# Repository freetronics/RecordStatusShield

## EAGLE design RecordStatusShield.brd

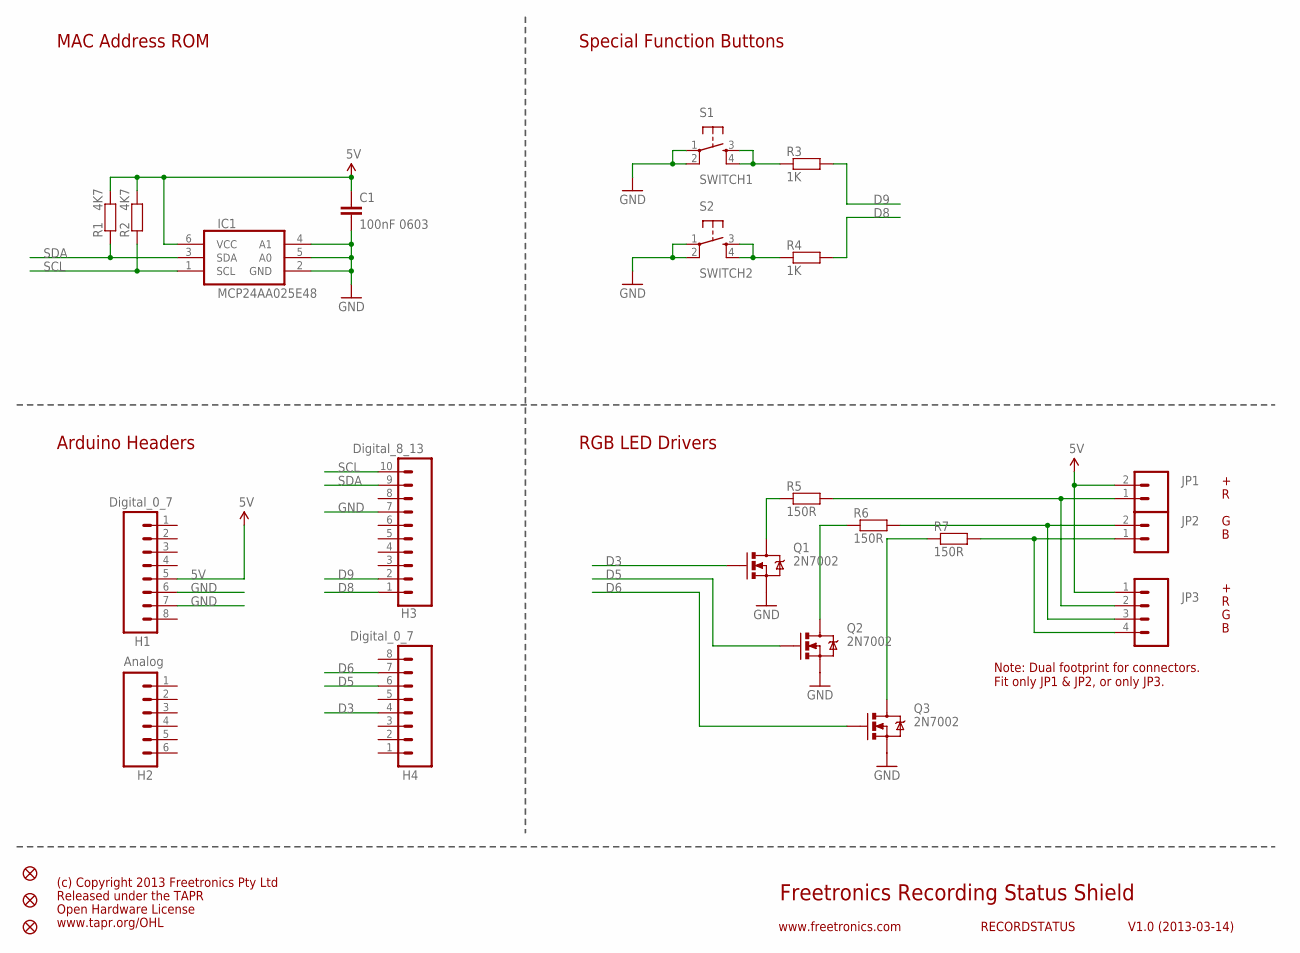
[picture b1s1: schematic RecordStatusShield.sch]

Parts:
C1: 100nF 0603; C0603
FID5, FID6, FID7: FIDUCIAL1X2.5; FIDUCIAL-1X2.5
H1, H4: Digital_0_7; 1X08
H2: Analog; 1X06
H3: Digital_8_13; 1X10
IC1: MCP24AA025E48; SOT23-6
JP1, JP2: M025MM; SCREWTERMINAL-5MM-2
JP3: M04PTH; 1X04
Q1, Q2, Q3: 2N7002; SOT23-3
R1, R2: 4K7; 0603
R3, R4: 1K; 0603
R5, R6, R7: 150R; 0603
S1: SWITCH1; TACTILE-PTH
S2: SWITCH2; TACTILE-PTH

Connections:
5V: C1.1, H1.5, IC1.6 (VCC), JP1.2, JP3.1, R1.2, R2.2
D3: H4.4, Q1.1 (G)
D5: H4.6, Q2.1 (G)
D6: H4.7, Q3.1 (G)
D8: H3.1, R4.2
D9: H3.2, R3.2
GND: C1.2, H1.6, H1.7, H3.7, IC1.2 (GND), IC1.4 (A1), IC1.5 (A0), Q1.2 (S), Q2.2 (S), Q3.2 (S), S1.1, S1.2, S2.1, S2.2
unnamed: R3.1, S1.3, S1.4
unnamed: R4.1, S2.3, S2.4
unnamed: JP2.1, JP3.4, R7.2
unnamed: JP2.2, JP3.3, R6.2
unnamed: JP1.1, JP3.2, R5.2
unnamed: Q1.3 (D), R5.1
unnamed: Q2.3 (D), R6.1
unnamed: Q3.3 (D), R7.1
SCL: H3.10, IC1.1 (SCL), R2.1
SDA: H3.9, IC1.3 (SDA), R1.1

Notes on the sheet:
Freetronics Recording Status Shield
V1.0 (2013-03-14)
www.freetronics.com
RECORDSTATUS
Arduino Headers
MAC Address ROM
Special Function Buttons
RGB LED Drivers
Released under the TAPR
Open Hardware License
www.tapr.org/OHL
(c) Copyright 2013 Freetronics Pty Ltd
Note: Dual footprint for connectors. Fit only JP1 & JP2, or only JP3.

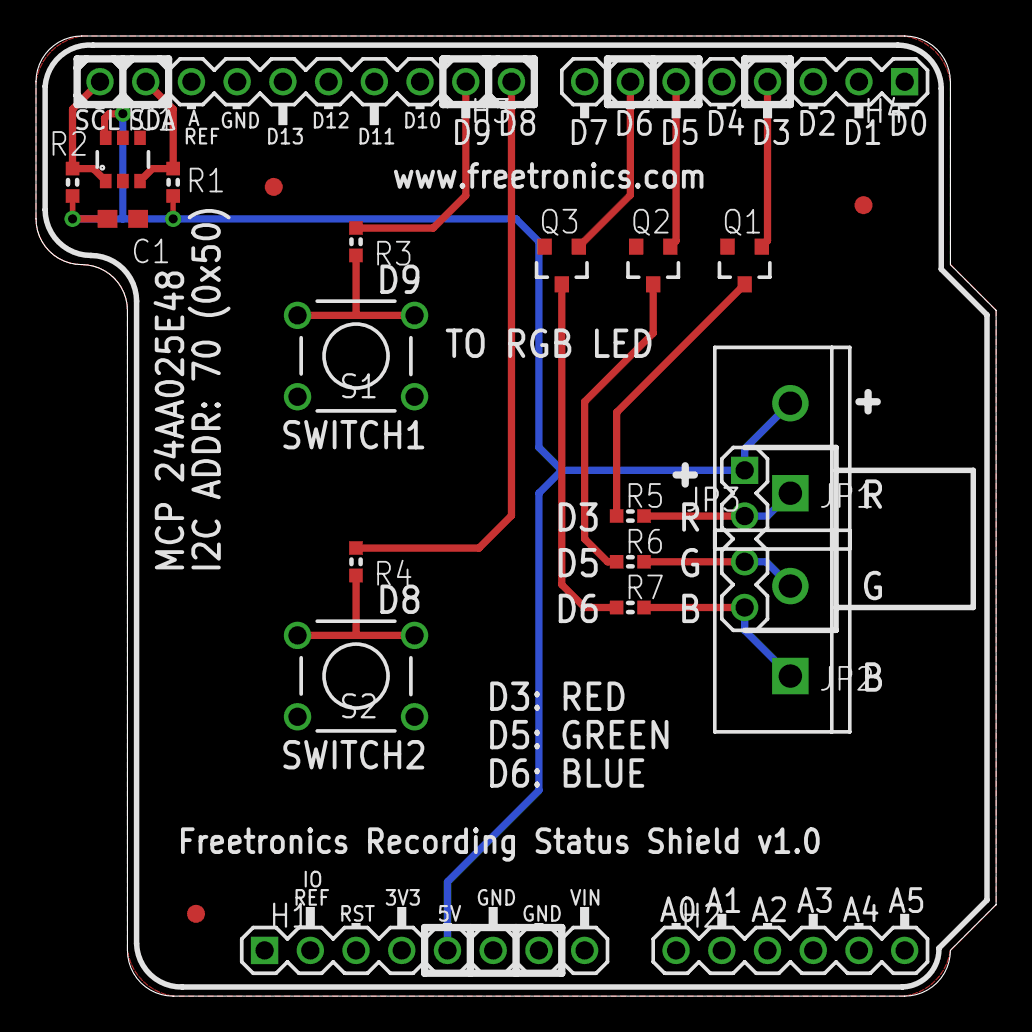
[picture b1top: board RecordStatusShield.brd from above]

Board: 2 copper layers, 53.3 x 53.3 mm, 24 parts (0 on the bottom side), 17 nets.

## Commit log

2019-04-24 Imported old project files from 2013

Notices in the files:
RecordStatusShield.brd:
(c) 2013 Freetronics Pty Ltd
parts and their libraries:
freetronics-original: Licensing: CC v3.0 Share-Alike You are welcome to use this library for commercial purposes.
